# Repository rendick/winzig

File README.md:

# Winzig

Winzig is a handheld gaming console based on Raspberry Pi Pico, which supports the Lua programming language for developing games.

# To-Do

- Add buzzer for sound output
- Add extra two buttons for up and down movement
- Implement the support for the use of Li-ion batteries

# License

MIT

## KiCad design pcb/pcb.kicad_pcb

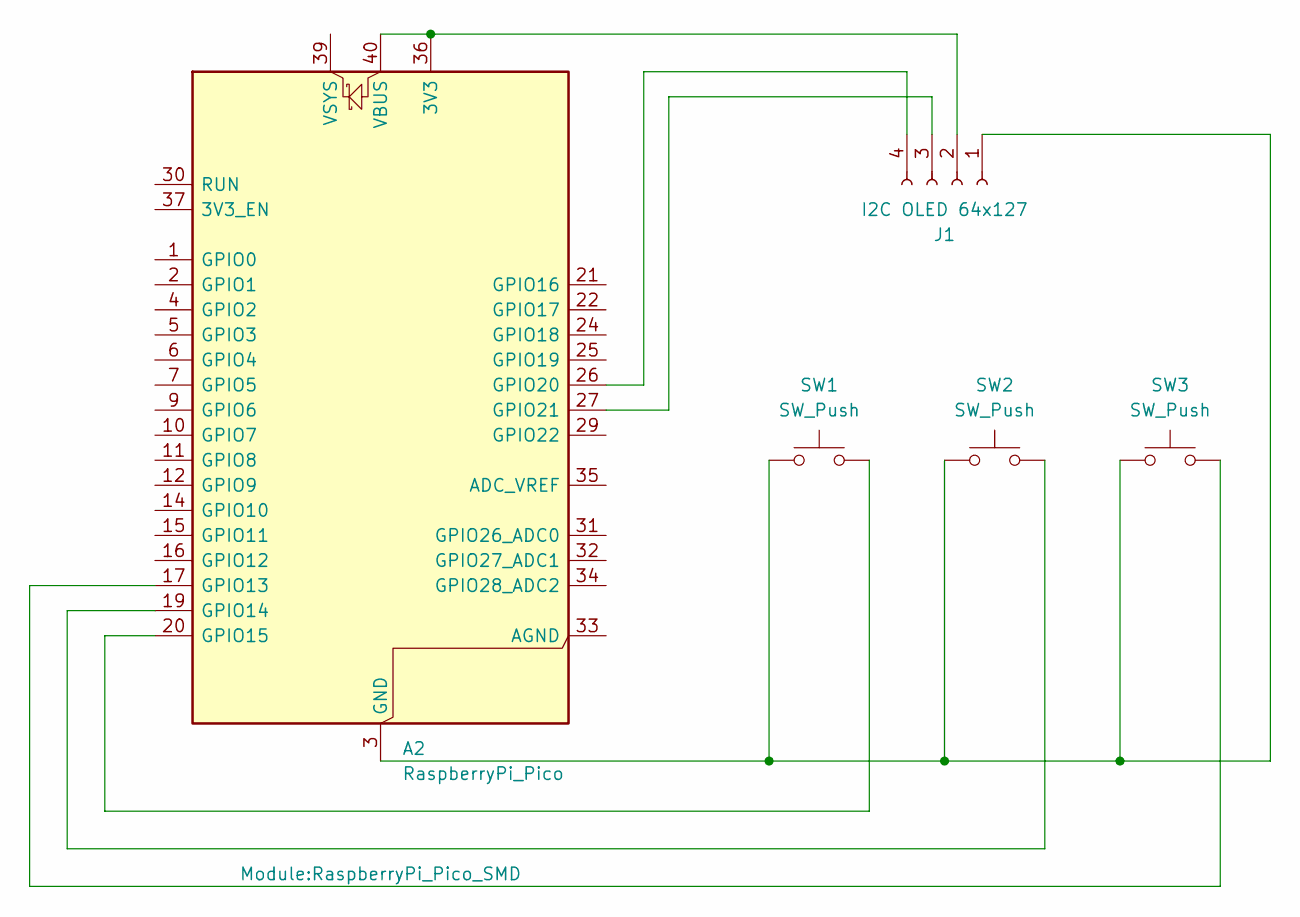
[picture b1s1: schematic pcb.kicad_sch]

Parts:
A2: RaspberryPi_Pico; RaspberryPi_Pico_SMD
J1: I2C OLED 64x127; PinHeader_1x04_P2.54mm_Vertical
SW1, SW2, SW3: SW_Push; SW_PUSH_6mm_H7.3mm

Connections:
unnamed: A2.36 (3V3), A2.40 (VBUS), J1.2 (VCC)
unnamed: A2.17 (GPIO13), SW3.2
unnamed: A2.19 (GPIO14), SW2.2
unnamed: A2.20 (GPIO15), SW1.2
unnamed: A2.26 (GPIO20), J1.4 (SDA)
unnamed: A2.27 (GPIO21), J1.3 (SCL)
unnamed: A2.3 (GND), A2.8 (GND), A2.13 (GND), A2.18 (GND), A2.23 (GND), A2.28 (GND), A2.38 (GND), J1.1 (GND), SW1.1, SW2.1, SW3.1

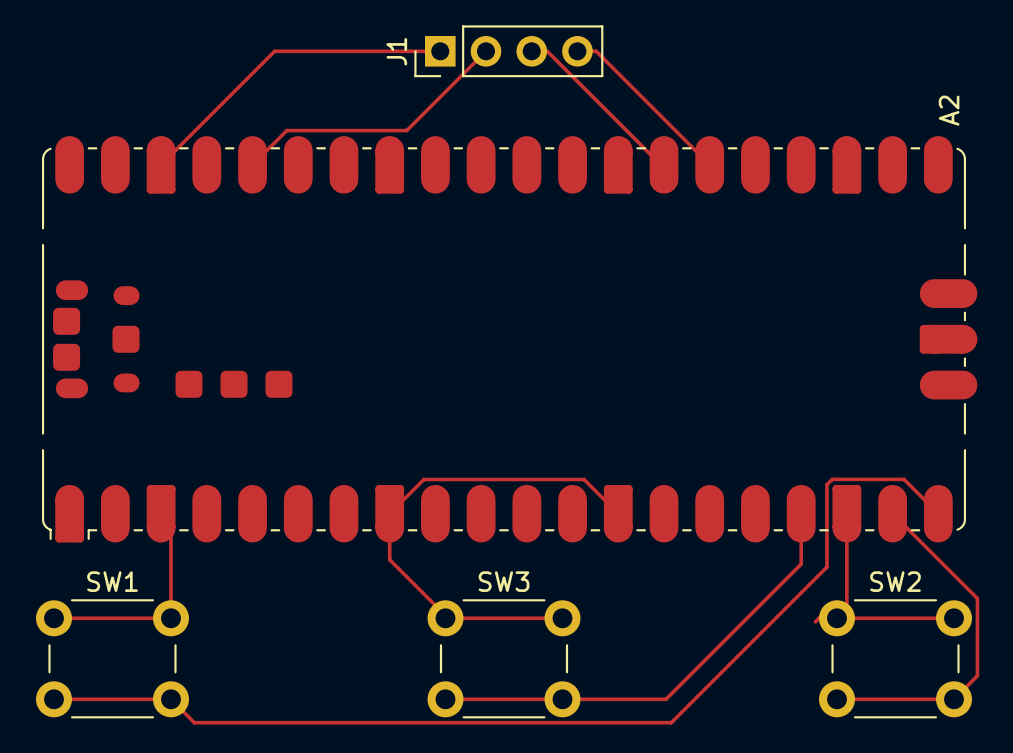
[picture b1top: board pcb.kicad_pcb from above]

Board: 2 copper layers, 5 parts (0 on the bottom side), 7 nets.

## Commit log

2026-01-06 winzig.cpp: implement a modification button
2026-01-08 PCB: initial design
2026-01-20 feat: calculate the ball's angle according to the hitting point
2026-01-23 feat: Lua support
2026-01-26 fix: move winzig.cpp to src/
2026-01-26 feat: allow Lua to call C functions
2026-01-26 feat: implement SD card support
2026-01-26 fix: fix syntax errors
2026-01-27 style: implement clang-format
2026-01-27 feat: sort files
2026-01-27 feat: add the ability to control GPIO pins in Lua
2026-01-27 style: improve clang-format
2026-01-28 feat: extern Lua support
2026-01-30 feat: improve SD card functions
2026-02-01 feat: improve user interface
2026-02-24 fix: disable SD card GPIO detector
2026-02-24 feat: improve SD card implementation
2026-02-24 feat: implement the execution of Lua file in the menu
2026-02-26 feat: add macros for I2C GPIO pins
2026-02-26 fix: correct cursor movement
2026-03-04 style: add README
2026-03-04 docs: update README
